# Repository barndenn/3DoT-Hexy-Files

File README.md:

# Hexy To Do List
- Test new pinouts using a 3DoT board 
- Order PCBs 
- Assemble the shield 
- Test the shield 
- Figure out how to turn without bobbing 

# Pin Initialization
|Shield Input|Pin Configurations|Pin # (Arduino)|Pin # (ATmega32U4)|
|---|---|---|---|
|Shaft Encoder L (OUT A)|PDO/PCINT3/MISO|D14|PB3|
|Shaft Encoder L (OUT B)|PDI/PCINT2/MOSI|D16|PB2|
|Shaft Encoder R (OUT A)|PCINT1/SCLK|D15|PB1|
|Shaft Encoder R (OUT B)|SS/PCINT0|D17|PB0|
|Gear Sens L|SDA/INT1|D2|PD1|
|Gear Sens R|OC0B/SCL/INT0|D3|PD0

Shaft Encoder inputs will be read from a pin change interrupt. Gear sensors can be read using analogRead on any digital pin.

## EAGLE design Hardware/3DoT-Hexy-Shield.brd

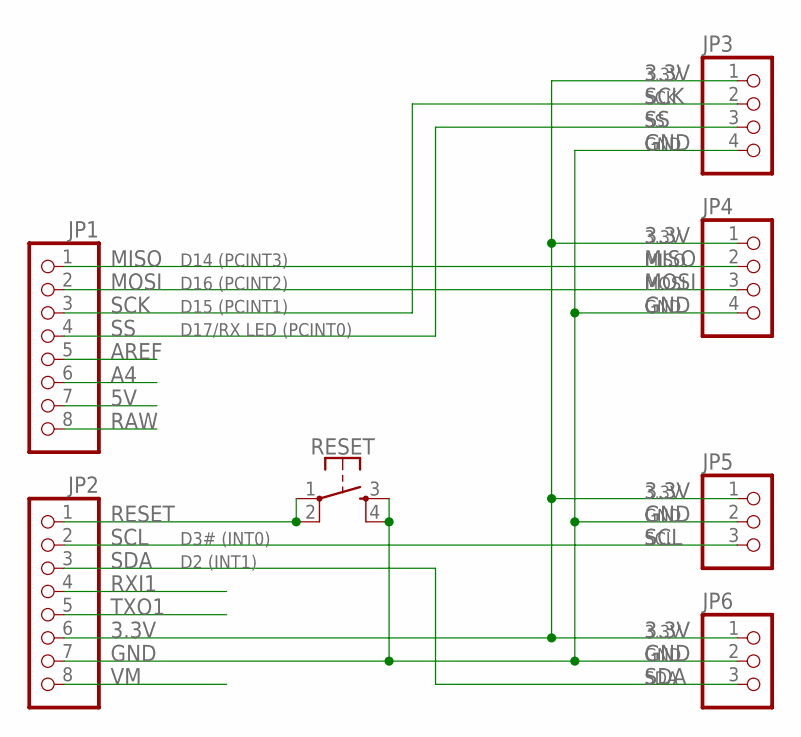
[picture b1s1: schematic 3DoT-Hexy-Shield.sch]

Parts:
JP1, JP2: PINHD-1X8; 1X08
JP3, JP4: PINHD-1X4; 1X04
JP5, JP6: PINHD-1X3; 1X03
RESET: MOMENTARY-SWITCH-SPST-2-SMD-5.2MM; TACTILE_SWITCH_SMD_5.2MM

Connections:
3.3V: JP2.6, JP3.1, JP4.1, JP5.1, JP6.1
5V: JP1.7
A4: JP1.6
AREF: JP1.5
GND: JP2.7, JP3.4, JP4.4, JP5.2, JP6.2, RESET.3, RESET.4
MISO: JP1.1, JP4.2
MOSI: JP1.2, JP4.3
RAW: JP1.8
RESET: JP2.1, RESET.1, RESET.2
RXI1: JP2.4
SCK: JP1.3, JP3.2
SCL: JP2.2, JP5.3
SDA: JP2.3, JP6.3
SS: JP1.4, JP3.3
TXO1: JP2.5
VM: JP2.8

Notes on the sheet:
D15 (PCINT1)
D17/RX LED (PCINT0)
D16 (PCINT2)
D14 (PCINT3)
D3# (INT0)
D2 (INT1)

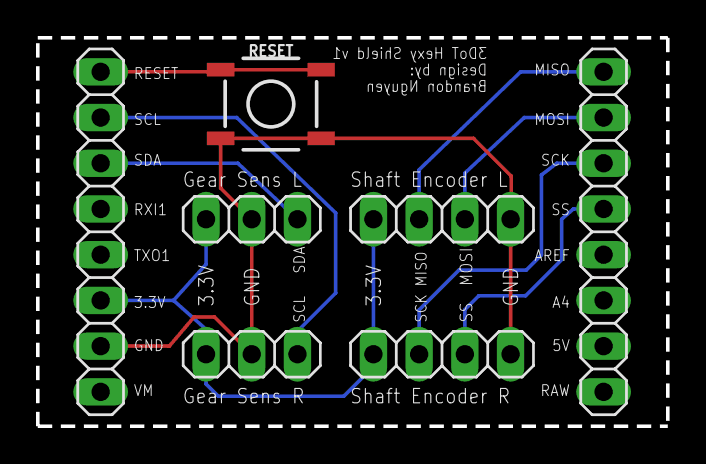
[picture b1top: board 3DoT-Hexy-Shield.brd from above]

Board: 2 copper layers, 35.0 x 21.6 mm, 7 parts (0 on the bottom side), 9 nets.

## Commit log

2019-06-06 adding hardware files and reorganizing repo
2019-06-06 Finished board layout for the shield
2019-06-07 changed names, const int -> #define
2019-11-05 Changed pin mapping

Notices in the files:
parts and their libraries:
SparkFun-Switches: Licensing: Creative Commons ShareAlike 4.0 International - https://creativecommons.org/licenses/by-sa/4.0
